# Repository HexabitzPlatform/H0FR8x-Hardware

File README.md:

# H0FR8x-Hardware
Hexabitz AC Dimmer Module Hardware Design

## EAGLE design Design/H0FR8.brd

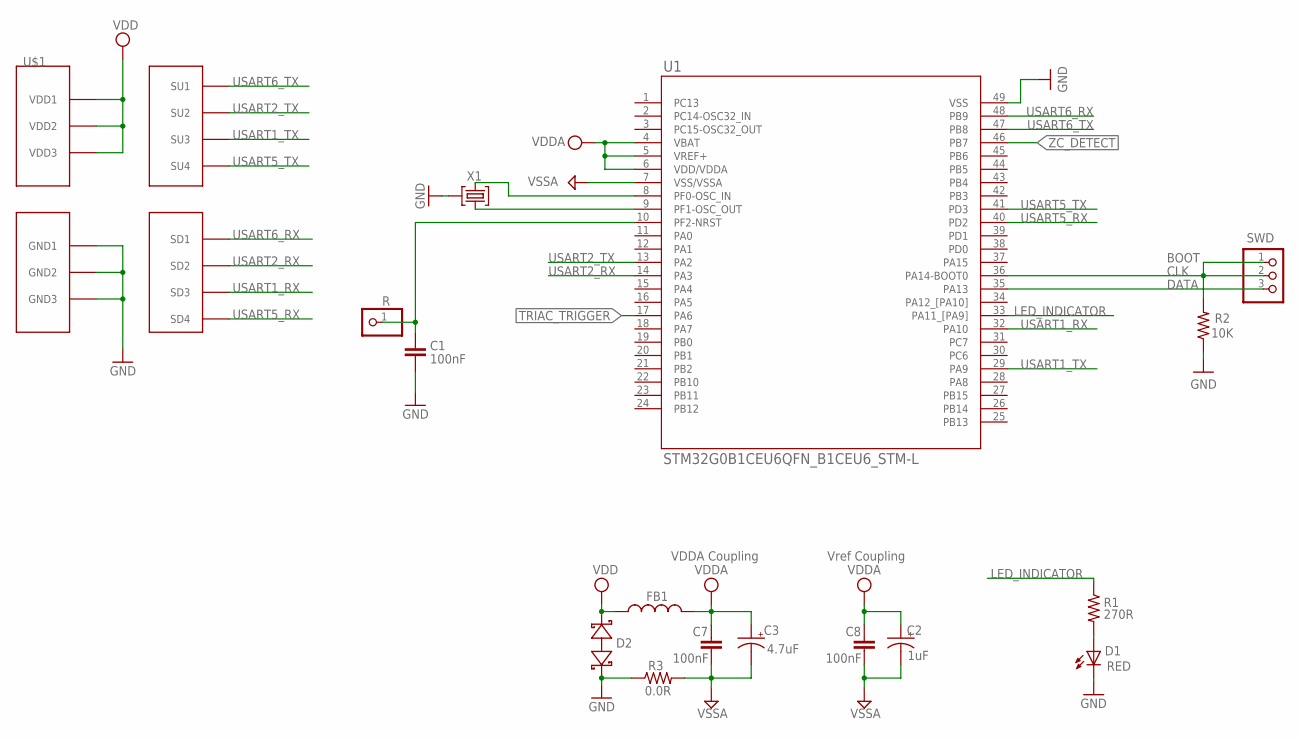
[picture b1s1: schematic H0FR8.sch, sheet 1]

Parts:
C1, C7, C8: 100nF; C-0603
C2: 1uF; C-0805-POL; TOLERANCE 10%; VOLTAGE_RATING 16V; MPN CC0805KKX7R7BB105
C3: 4.7uF; C-0805-POL; TOLERANCE 10%; VOLTAGE_RATING 25V; MPN GRM21BC81E475KA12L
D1: RED; VLMS1300-GS08; MPN VLMS1300-GS08
D2: BOURNS_CDSOD323-T03SCBOURNS_CDSOD323-T03SC_0_0; BOURNS_CDSOD323-T03SC_0
FB1: FB-0603
R: R; 1X01
R1: 270R; R-0603
R2: 10K; R-0603
R3: 0.0R; R-0603
SWD: PINHD-1X3; 1X03
TRIMBLE-LOGO2: HEXA-LOGO
U1: STM32G0B1CEU6QFN_B1CEU6_STM-L; QFN_B1CEU6_STM-L
U$1: HEXABIT_17.32_X3_NO_P1_P2_P3_P4_P5_P6_P11_P12
X1: XTALL_CSTCE8M00G52

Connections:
CLK: R2.2, SWD.1, SWD.2, U1.36 (PA14-BOOT0)
DATA: SWD.3, U1.35 (PA13)
GND: C1.2, D1.C, D2.2 (C), R2.1, R3.1, U1.49 (VSS), U$1.PAD_PD12 (GND1), U$1.PAD_PD17 (GND2), U$1.PAD_PD19 (GND3), X1.P$2 (2); also elsewhere on the board
LED_INDICATOR: R1.1, U1.33 (PA11_[PA9])
unnamed: D1.A, R1.2
unnamed: C1.1, R.1, U1.10 (PF2-NRST)
unnamed: U1.9 (PF1-OSC_OUT), X1.P$1 (1)
unnamed: U1.8 (PF0-OSC_IN), X1.P$3 (3)
TRIAC_TRIGGER: U1.17 (PA6); also elsewhere on the board
USART1_RX: U1.32 (PA10), U$1.PAD_PD2 (SD3)
USART1_TX: U1.29 (PA9), U$1.PAD_PU2 (SU3)
USART2_RX: U1.14 (PA3), U$1.PAD_PD1 (SD2)
USART2_TX: U1.13 (PA2), U$1.PAD_PU1 (SU2)
USART5_RX: U1.40 (PD2), U$1.PAD_PD8 (SD4)
USART5_TX: U1.41 (PD3), U$1.PAD_PU8 (SU4)
USART6_RX: U1.48 (PB9), U$1.PAD_PD3 (SD1)
USART6_TX: U1.47 (PB8), U$1.PAD_PU3 (SU1)
VDD: D2.1 (A), FB1.1, U$1.PAD_PU12 (VDD1), U$1.PAD_PU17 (VDD2), U$1.PAD_PU19 (VDD3); also elsewhere on the board
VDDA: C2.1 (+), C3.1 (+), C7.1, C8.1, FB1.2, U1.4 (VBAT), U1.5 (VREF+), U1.6 (VDD/VDDA)
VSSA: C2.2 (-), C3.2 (-), C7.2, C8.2, R3.2, U1.7 (VSS/VSSA)
ZC_DETECT: U1.46 (PB7); also elsewhere on the board

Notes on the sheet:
Vref Coupling
VDDA Coupling
BOOT

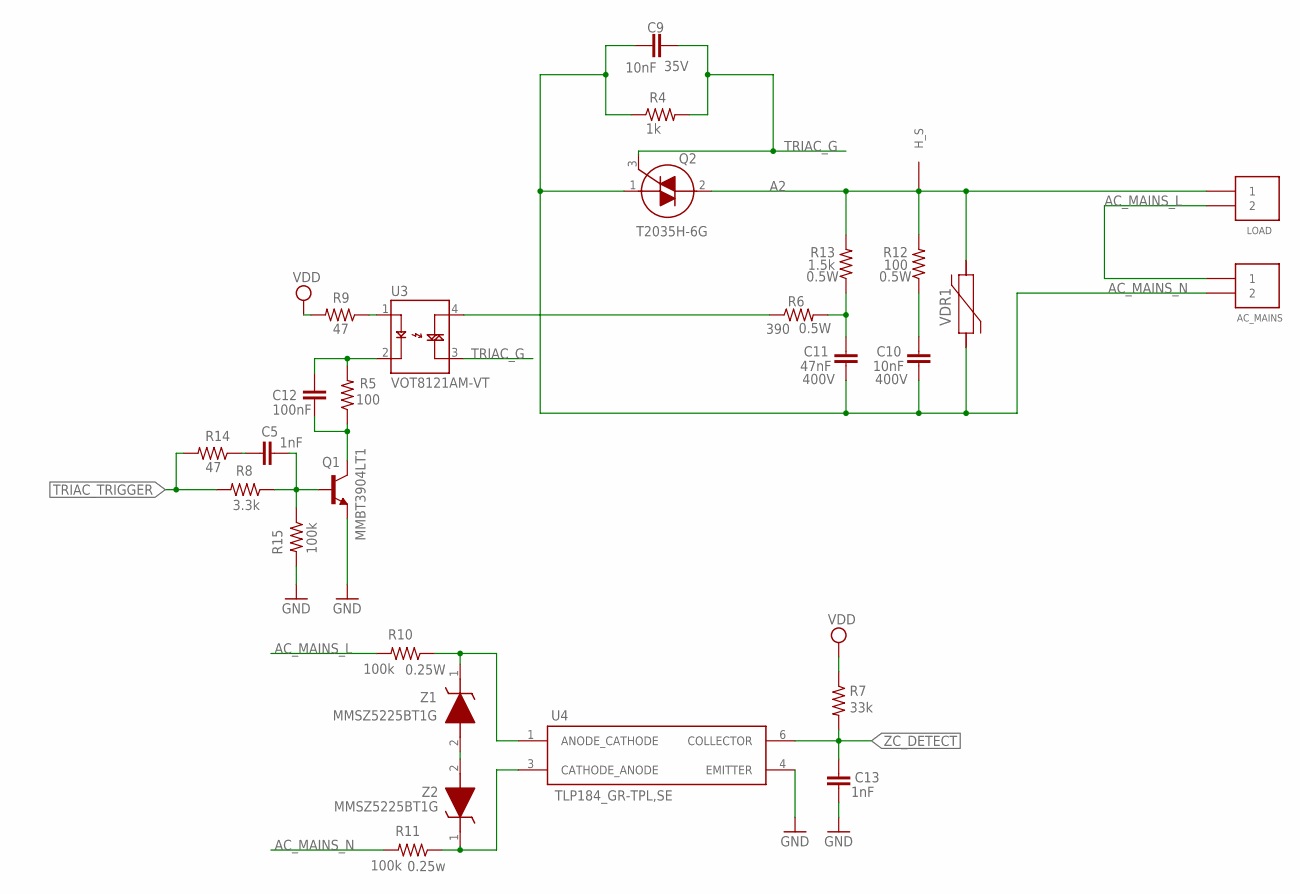
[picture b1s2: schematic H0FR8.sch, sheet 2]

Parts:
AC_MAINS: 1546111-2
C5, C13: 1nF; C-0603
C9: 10nF; C-0603; VOLTAGE_RATING 35V
C10: 10nF; C-0805; VOLTAGE_RATING 400V; MPN C2012X7T2W103M085AA
C11: 47nF; C-0805; VOLTAGE_RATING 400V; MPN C2012X7T2W473K125AA
C12: 100nF; C-0603
LOAD: 1546111-2
Q1: MMBT3904LT1; VOLTAGE_RATING_DC 40.0 V; MPN MMBT3904LT1G
Q2: T2035H-6G; T2035H6G
R4: 1k; R-0603
R5: 100; R-0603; TOLERANCE ±1%; MPN RC0402FR-07100RL
R6: 390; R-0805; MPN ERJ-P06J391V
R7: 33k; R-0603; TOLERANCE ±1%; MPN RC0402FR-07100RL
R8: 3.3k; R-0603; TOLERANCE ±5%; MPN RC0603JR-070RL
R9, R14: 47; R-0603; TOLERANCE ±1%; MPN RC0402FR-07100RL
R10: 100k; R-0805; TOLERANCE ±5%; MPN RC0603JR-070RL
R11: 100k; R-0805; MPN ERJ-P06J104V
R12: 100; R-0805; MPN ERJ-P06J101V
R13: 1.5k; R-0805; MPN ERJ-P06J152V
R15: 100k; R-0603; TOLERANCE ±5%; MPN RC0603JR-070RL
U3: VOT8121AM-VT; SOIC254P675X240-4N
U4: TLP184_GR-TPL,SE; SOIC254P700X230-4N
U$2: FK244D2PAK
VDR1: V275LA4P; LA_07MM_LOW_LTF
Z1, Z2: MMSZ5225BT1G; SOD3716X135N

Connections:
A2: LOAD.1, Q2.2 (MT2), R12.2, R13.2, U$2.P$1, U$2.P$2, VDR1.2
AC_MAINS_L: AC_MAINS.1, LOAD.2, R10.2
AC_MAINS_N: AC_MAINS.2, C9.2, C10.2, C11.2, Q2.1 (MT1), R4.1, R11.2, VDR1.1
GND: C13.2, Q1.2 (E), R15.2, U4.4 (EMITTER); also elsewhere on the board
unnamed: R9.1, U3.1 (A)
unnamed: C10.1, R12.1
unnamed: C11.1, R6.2, R13.1
unnamed: R6.1, U3.4 (MT2)
unnamed: C5.2, R14.1
unnamed: C12.1, R5.2, U3.2 (C)
unnamed: C12.2, Q1.3 (C), R5.1
unnamed: Z1.2 (A), Z2.2 (A)
unnamed: C5.1, Q1.1 (B), R8.1, R15.1
unnamed: R10.1, U4.1 (ANODE_CATHODE), Z1.1 (K)
unnamed: R11.1, U4.3 (CATHODE_ANODE), Z2.1 (K)
TRIAC_G: C9.1, Q2.3 (G), R4.2, U3.3 (MT1)
TRIAC_TRIGGER: R8.2, R14.2; also elsewhere on the board
VDD: R7.1, R9.2; also elsewhere on the board
ZC_DETECT: C13.1, R7.2, U4.6 (COLLECTOR); also elsewhere on the board

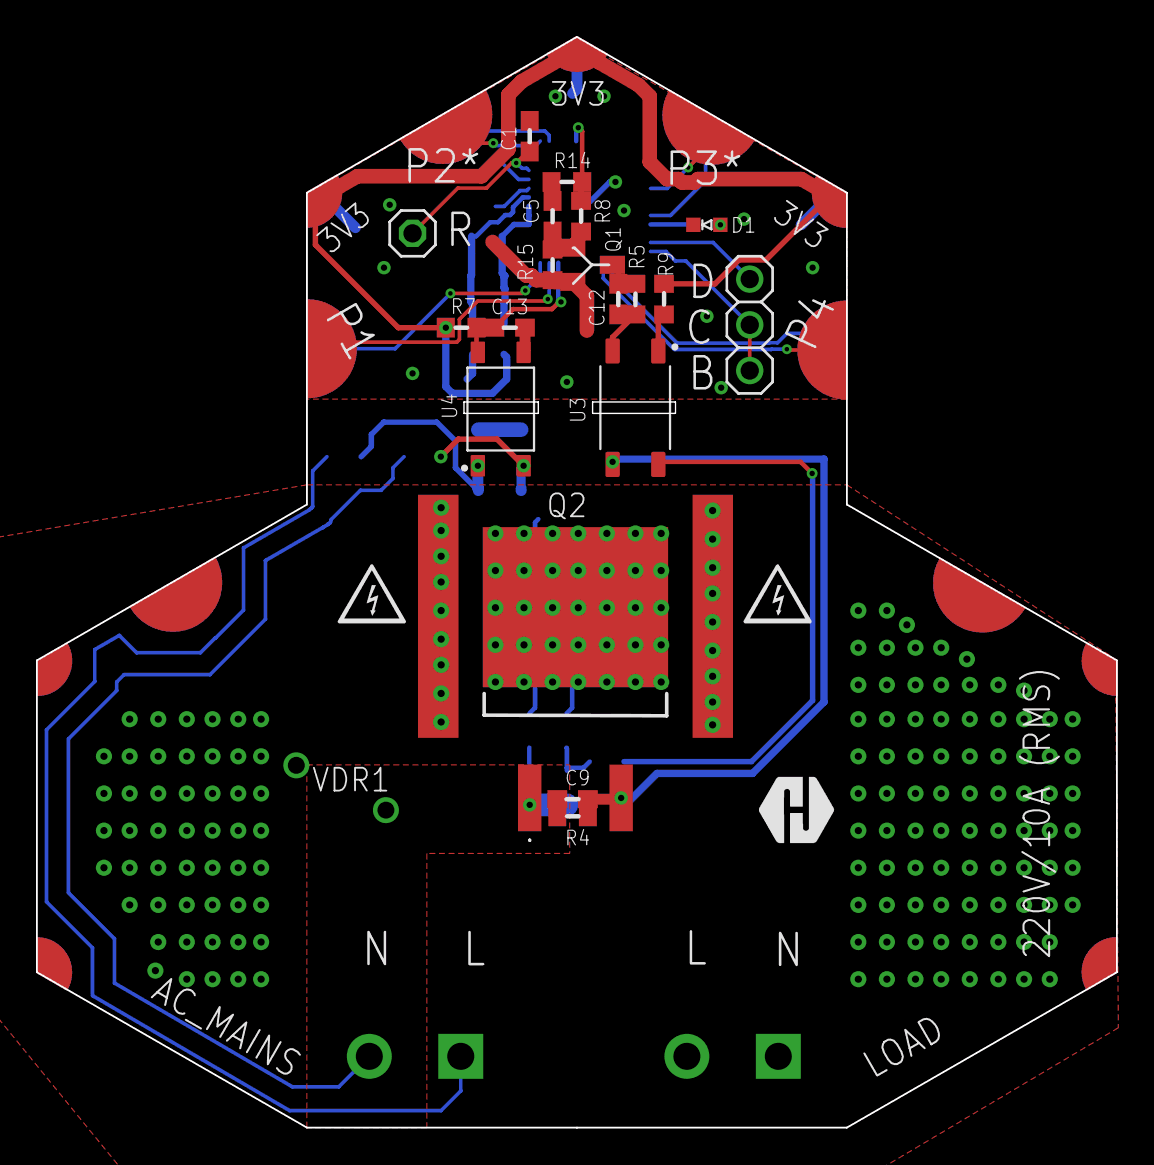
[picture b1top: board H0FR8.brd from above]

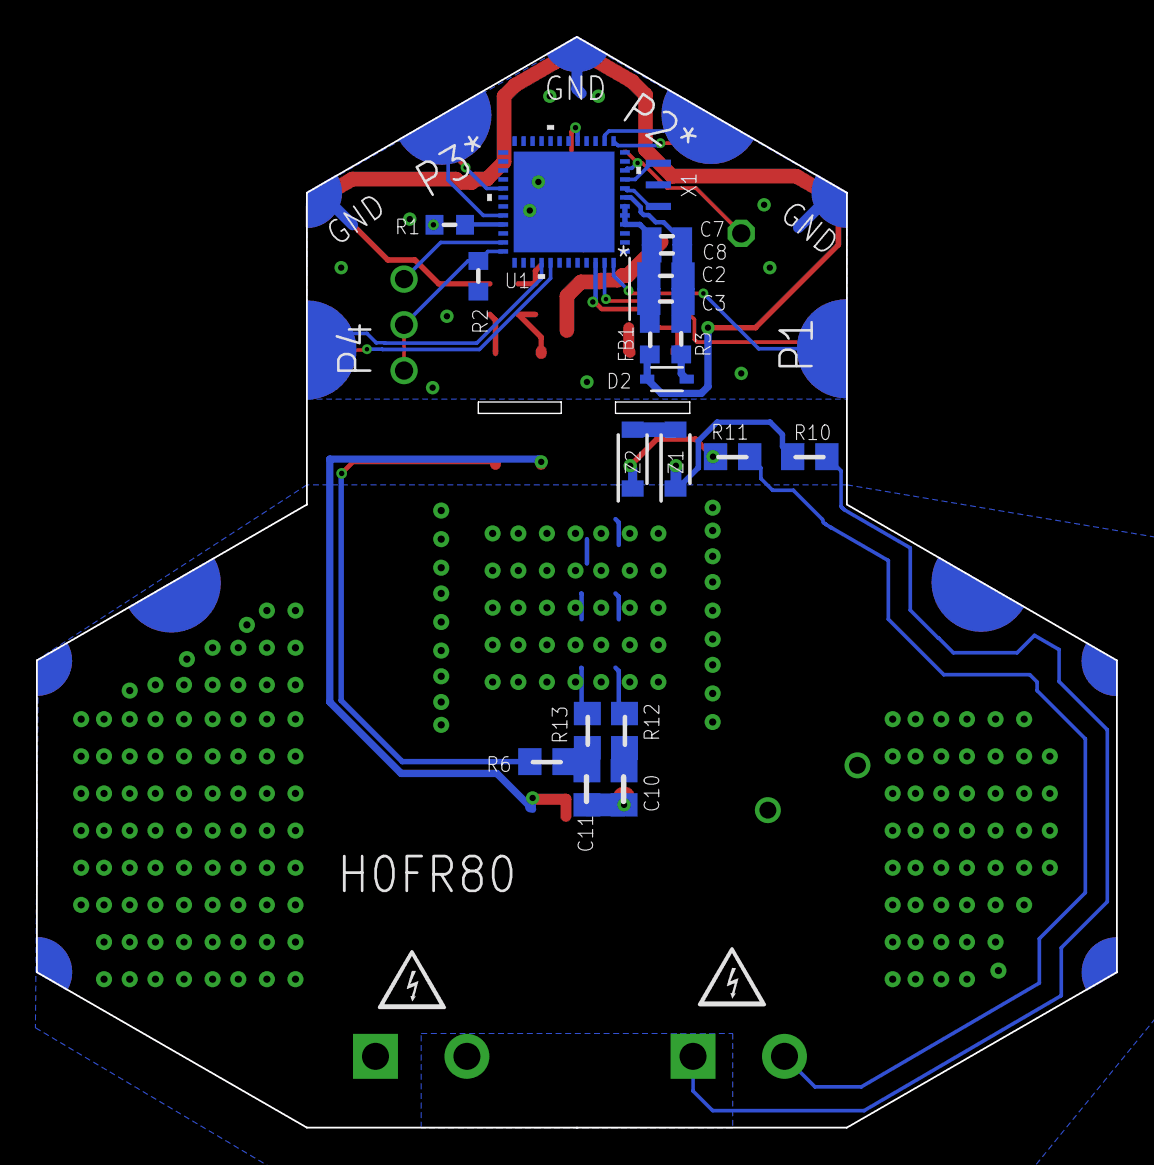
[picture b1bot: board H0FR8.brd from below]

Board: 2 copper layers, 60.0 x 60.6 mm, 45 parts (20 on the bottom side), 36 nets.

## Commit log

2024-05-05 Create the template
2024-05-06 TEST
2024-05-06 Stage1
2024-05-07 stage2
2024-05-08 Final schematic design
2024-05-09 Schematic modification
2024-06-01 Edit the description
2024-11-09 Intial Layout Design
2024-11-13 - Fixed component's footprints and 3d packages.
2024-11-13 - Intial PCB design.
2024-11-16 - Silkscreen layer is done.
2024-11-21 - Changed connector. - Fixed nets. - new pcb layout.
2024-11-26 - Silkscreen is done. - Alligned vias.
2024-11-26 - Generated BOM and Documentation.
2024-11-29 - Changed components description in BOM - Fixed issues in Layout - Fixed issues in Schematic - Generated new documentation
2024-12-14 - Rearranged components in BOM
2024-12-14 - Changed layout - Rearranged components in BOM
2024-12-18 -The final design, all done.

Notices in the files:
parts and their libraries:
COPYRIGHT: Copyright (C) 2021 Ultra Librarian. All rights reserved.
COPYRIGHT: Copyright (C) 2024 Ultra Librarian. All rights reserved.
